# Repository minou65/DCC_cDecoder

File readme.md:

# cDecoder
## Inhalt
- [cDecoder](#cdecoder)
  - [Inhalt](#inhalt)
  - [Funktionen](#funktionen)
  - [Programmierung](#programmierung)
  - [Analog Betrieb](#analog-betrieb)
  - [Immer ein](#immer-ein)
  - [Powerpack](#powerpack)
  - [Dimmen der Ausgänge](#dimmen-der-ausgänge)
  - [Anschlüsse](#anschlüsse)
    - [fDecoder](#fdecoder)
    - [cDecoder](#cdecoder-1)
    - [PowerPack](#powerpack-1)
    - [Farben](#farben)
  - [Lange DCC Adresse](#lange-dcc-adresse)
  - [CV Tabelle](#cv-tabelle)
    - [Zuordnung Ausgänge zu Funktionstasten](#zuordnung-ausgänge-zu-funktionstasten)
    - [Funktion aktiv bei](#funktion-aktiv-bei)
    - [Modus der Ausgänge](#modus-der-ausgänge)
      - [Blinker On Time](#blinker-on-time)
      - [Blinker off Time](#blinker-off-time)
      - [Dimmen der Ausgänge](#dimmen-der-ausgänge-1)
      - [Automatisches abschalten](#automatisches-abschalten)
  - [Beispiele](#beispiele)
  - [Programmieren des prozessors](#programmieren-des-prozessors)

## Funktionen
- Ein/Aus
- Impuls
- Blinker

Der Attiny85 untersützt nur 5 Ausgänge. Die Funktionen sind auf die Ausgänge verteilt. Die Funktionen können über die CV's 66 - 70 eingestellt werden. 
Die Blinkerfunktion kann über die CV's 71 - 75 eingestellt werden. Die Zeit für das Blinken kann über die CV's 76 - 80 eingestellt werden. 
Die Zeit wird in 10ms Schritten angegeben. Die Helligkeit der Ausgänge kann über die CV's 81 und 82 eingestellt werden. 
Die Zeit für das automatische abschalten kann über die CV's 86 - 90 eingestellt werden. Die Zeit wird in 10ms Schritten angegeben.

## Programmierung
Um den Decoder auf dem Programmiergleis programmieren zu können muss eine Last an AUX 1 angeschlossen werden, die mindestens einen Strom von 60mA erzeugt.

## Analog Betrieb
Wird während 100ms kein DCC Signal erkannt, werden die Funktionen gemäss CV 13 aktiviert

## Immer ein
Ab Version 3 untersützt die Firmware CV 123, damit können Ausgänge definiert werden, welche beim anlagen einer Spannung sofort eingeschaltet werden.
Eingeführt für die Rheinbrücke beim Modell Eisenbahn Club Seebezirk (MECS), Fräschels (CH)

## Powerpack
Ein externes Powerpack kann an den Decoder angeschlossen werden. Dazu können die Pad's VCC und GND auf der Rückseite des Decoders verwendet werden.

## Dimmen der Ausgänge
Die Ausgänge AUX 1 und AUX 2 können gedimmt werden. Die Helligkeit kann über CV 81 und 82 eingestellt werden.

## Anschlüsse
### fDecoder
| oben | unten |
|---|---|
|  |  |
| __v2__ <br>  | |

### cDecoder
| oben | unten |
|---|---|
| ||

### PowerPack
| oben | unten |
|---|---|
|  ||

### Farben
| Draht | Verwendung |
|--------|--------------|
| Rot | Rail |
| Braun | Rail |
| Blau | Decoder + |
| Weiss | Aux 1 / Licht vorne |
| Gelb | Aux 2 / Licht hinten |
| Violett | Aux 3 |
| Grün | Aux 4 |
| Schwarz | GND |

## Lange DCC Adresse
Um die lange DCC-Adresse in die Register 17 und 18 umzurechnen, kann folgende Formel verwendet werden.<br><br>
CV 17 = Adresse / 256 (nur die Stellen vor dem Komma) + 192<br>
CV 18 = Adresse - ((CV 17 - 192) * 256)<br>

Die lange Adresse wird nur verwendet, wenn das Bit 5 in CV 29 gesetzt ist

Hier gibt es einen CV Rechner
https://www.opendcc.de/info/decoder/dcc_cv.html

## CV Tabelle
| Bezeichnung | CV | Wertbereich <br> (default) | Beschreibung |
|---|:--------:|---|---|
| Basisadresse | 1 | 1 - 255 (3) | Wertebereich im DCC-Format 1 - 127 |
| | 2 | 120 | |
| | 5 | 255 | |
| Version | 7 | | |
| Hersteller | 8 | | |
| Reset | 8 |  | Durch Eingeben eines Wertes 8, werden alle Einstellungen auf Default gesetzt |
| Im Analogbetrieb aktive Ausgänge | 13 | 0 - 255 (0) | AUX 1 ein = 1<br>AUX 2 ein = 2<br>AUX 3 ein = 4<br>AUX 4 ein = 8<br>AUX 5 ein = 16 |
| Decoderlock | 15 | 0 - 255 (0) | Decoder-Lock Funktion laut NMRA. <br>Details siehe http://www.nmra.org/standards/DCC/WGpublic/0305051/0305051.html |
| Decoderlock | 16 | 0 - 255 (0) | Decoder-Lock Funktion laut NMRA. <br>Details siehe http://www.nmra.org/standards/DCC/WGpublic/0305051/0305051.html |
| Erweiterte Adresse | 17 | 192 - 255 (0) | Nur für DCC-Format. Bei den meisten Zentralen ist es möglich, <br> erweiterte Adressendirekt einzugeben. Die CVs 17, 18 und 29 <br> werden von der Zentrale automatisch richtig eingestellt. |
| Erweiterte Adresse | 18 | 0 - 255 (3) |
| Konfigurationsdaten | 29 | 0 - 64 (2) | Fahrtrichtung Standard = 0 <br>Fahrtrichtung invertiert = 1 <br>14 Fahrstufen = 0 <br>28 oder 128 Fahrstufen 2 <br>Basisadressen = 0 <br>Erweiterte Adressen = 32 |
| Betriebszustand | 122 | 0/1 (0) | Den Betriebszustand der Ausgänge speichern. <br>0 = Aus <br>1 = Ein |
| Immer eingeschaltet<br>(ab Version 3) | 123 | 0 - 255 (0) | AUX 1 ein = 1<br>AUX 2 ein = 2<br>AUX 3 ein = 4<br>AUX 4 ein = 8<br>AUX 5 ein = 16 |

### Zuordnung Ausgänge zu Funktionstasten
| Bezeichnung | CV | Wertbereich <br> (default) | Beschreibung |
|---|:--------:|---|---|
| F0 | 30 | 0 - 31 (3) | AUX 1 = 1 <br> AUX 2 = 2 <br> AUX 3 = 4 <br> AUX 4 = 8 <br> AUX 5 = 16 |
| F1 | 31 | 0 - 31 (4) | |
| F2 | 32 | 0 - 31 (8) | |
| ... | ... | 0 - 31 (0) | |
| F28 | 58 | 0 - 31 (0) | |

### Funktion aktiv bei
| Bezeichnung | CV | Wertbereich <br> (default) | Beschreibung |
|---|:--------:|---|---|
| AUX 1 | 61 | 0 - 31 (1) | Vorwärts = 0 <br> Rückwärts = 1 <br> Beide = 3 <br> Default bei cDecoder ist 3 |
| AUX 2 | 62 | 0 - 31 (2) | Default bei cDecoder ist 3 |
| AUX 3 | 63 | 0 - 31 (3) | |
| AUX 4 | 64 | 0 - 31 (3) | |
| AUX 5 | 65 | 0 - 31 (3) | |

### Modus der Ausgänge
| Bezeichnung | CV | Wertbereich <br> (default) | Beschreibung |
|---|:--------:|---|---|
| AUX 1 | 66 | 0 - 31 (1) | Ein / Aus = 1 <br> Blinker = 2 <br> Impuls = 3 |
| AUX 2 | 67 | 0 - 31 (1) | |
| AUX 3 | 68 | 0 - 31 (1) | |
| AUX 4 | 69 | 0 - 31 (2) | |
| AUX 5 | 70 | 0 - 31 (2) | |

#### Blinker On Time
| Bezeichnung | CV | Wertbereich <br> (default) | Beschreibung |
|---|:--------:|---|---|
| AUX 1 | 71 | 0 - 255 (100) | Wert x 10 = Zeit in milli Sekunden |
| AUX 2 | 72 | 0 - 255 (100) | |
| AUX 3 | 73 | 0 - 255 (100) | |
| AUX 4 | 74 | 0 - 255 (100) | |
| AUX 5 | 75 | 0 - 255 (100) | |

#### Blinker off Time
| Bezeichnung | CV | Wertbereich <br> (default) | Beschreibung |
|---|:--------:|---|---|
| AUX 1 | 76 | 0 - 255 (100) | Wert x 10 = Zeit in milli Sekunden |
| AUX 2 | 77 | 0 - 255 (100) | |
| AUX 3 | 78 | 0 - 255 (100) | |
| AUX 4 | 79 | 0 - 255 (100) | |
| AUX 5 | 80 | 0 - 255 (100) | |

#### Dimmen der Ausgänge
| Bezeichnung | CV | Wertbereich <br> (default) | Beschreibung |
|---|:--------:|---|---|
| AUX 1 | 81 | 1 - 255 (255) | |
| AUX 2 | 82 | 1 - 255 (255) | |

#### Automatisches abschalten
| Bezeichnung | CV | Wertbereich <br> (default) | Beschreibung |
|---|:--------:|---|---|
| AUX 1 | 86 | 0 - 255 (0) | Wert x 10 = Zeit in milli Sekunden. Ist der <br> Wert grösser als 0 wird der Ausgang nach der <br> eingestellten Zeit wieder abgeschaltet. <br> Ist der Wert 0, dann bleibt der Ausgang eingeschaltet. |
| AUX 2 | 87 | 0 - 255 (0) | |
| AUX 3 | 88 | 0 - 255 (0) | |
| AUX 4 | 89 | 0 - 255 (0) | |
| AUX 5 | 90 | 0 - 255 (0) | |

## Beispiele
|Beispiel | Einstellungen |
|---|---|
| SBB Schlusslicht an AUX 4 <br><br><br><br> | CV64 = 36<br>CV69 = 27 <br>CV74 = 1 (On Time)<br>CV79 = 70 (Off Time) |
| Rheinbrücke MESC<br>Rote LED soll immer blinken<br><br><br> | CV123 = 1<br>CV66 = 2<br>CV71 = 80<br>76 = 20 |

## Programmieren des prozessors

Um den Prozessor zu programmieren wird ein ISP Programmer benötigt. Der Prozessor kann mit der Arduino IDE programmiert werden. Dazu muss der Prozessor als Board hinzugefügt werden.
- Dazu unter Datei -> Voreinstellungen -> Zusätzliche Boardverwalter-URLs: https://raw.githubusercontent.com/damellis/attiny/ide-1.6.x-boards-manager/package_damellis_attiny_index.json einfügen.
- Arduino AVR Boards installieren unter Werkzeuge -> Board -> Boardverwalter... -> Arduino AVR Boards installieren.
- In der Arduino IDE unter Werkzeuge -> Board -> Boardverwalter... -> attiny auswählen und installieren. 

Danach das Board wie folgt konfigurieren
    Board    : Attiny25/45/85
    Prozessor: Attiny85
    Clock    : Internal 16Mhz
    Programmer: Diamex USB ISP oder ATMEL STK500 (Für Windows 10 ist kein Treiber erforderlich)

Nun kann zuerst der Bootloader und danach die Firmware auf den Prozessor geschrieben werden. Unter visual Micro kommt folgende Fehlermeldung beim schreiben des Bootloaders

```
Error while burning bootloader.
Burn failed
avrdude: can't open input file aders/{bootloader.file}: No such file or directory
avrdude: read from file oaders/{bootloader.file}' failed
```

Dies ist normal, der Attiny hat keine Bootloader visual Micro sucht diesen aber und findet ihn nicht. Die Fuse und Clock settings werden aber geschrieben bevor der Bootloader geschrieben wird.
https://www.visualmicro.com/forums/YaBB.pl?num=1607630288

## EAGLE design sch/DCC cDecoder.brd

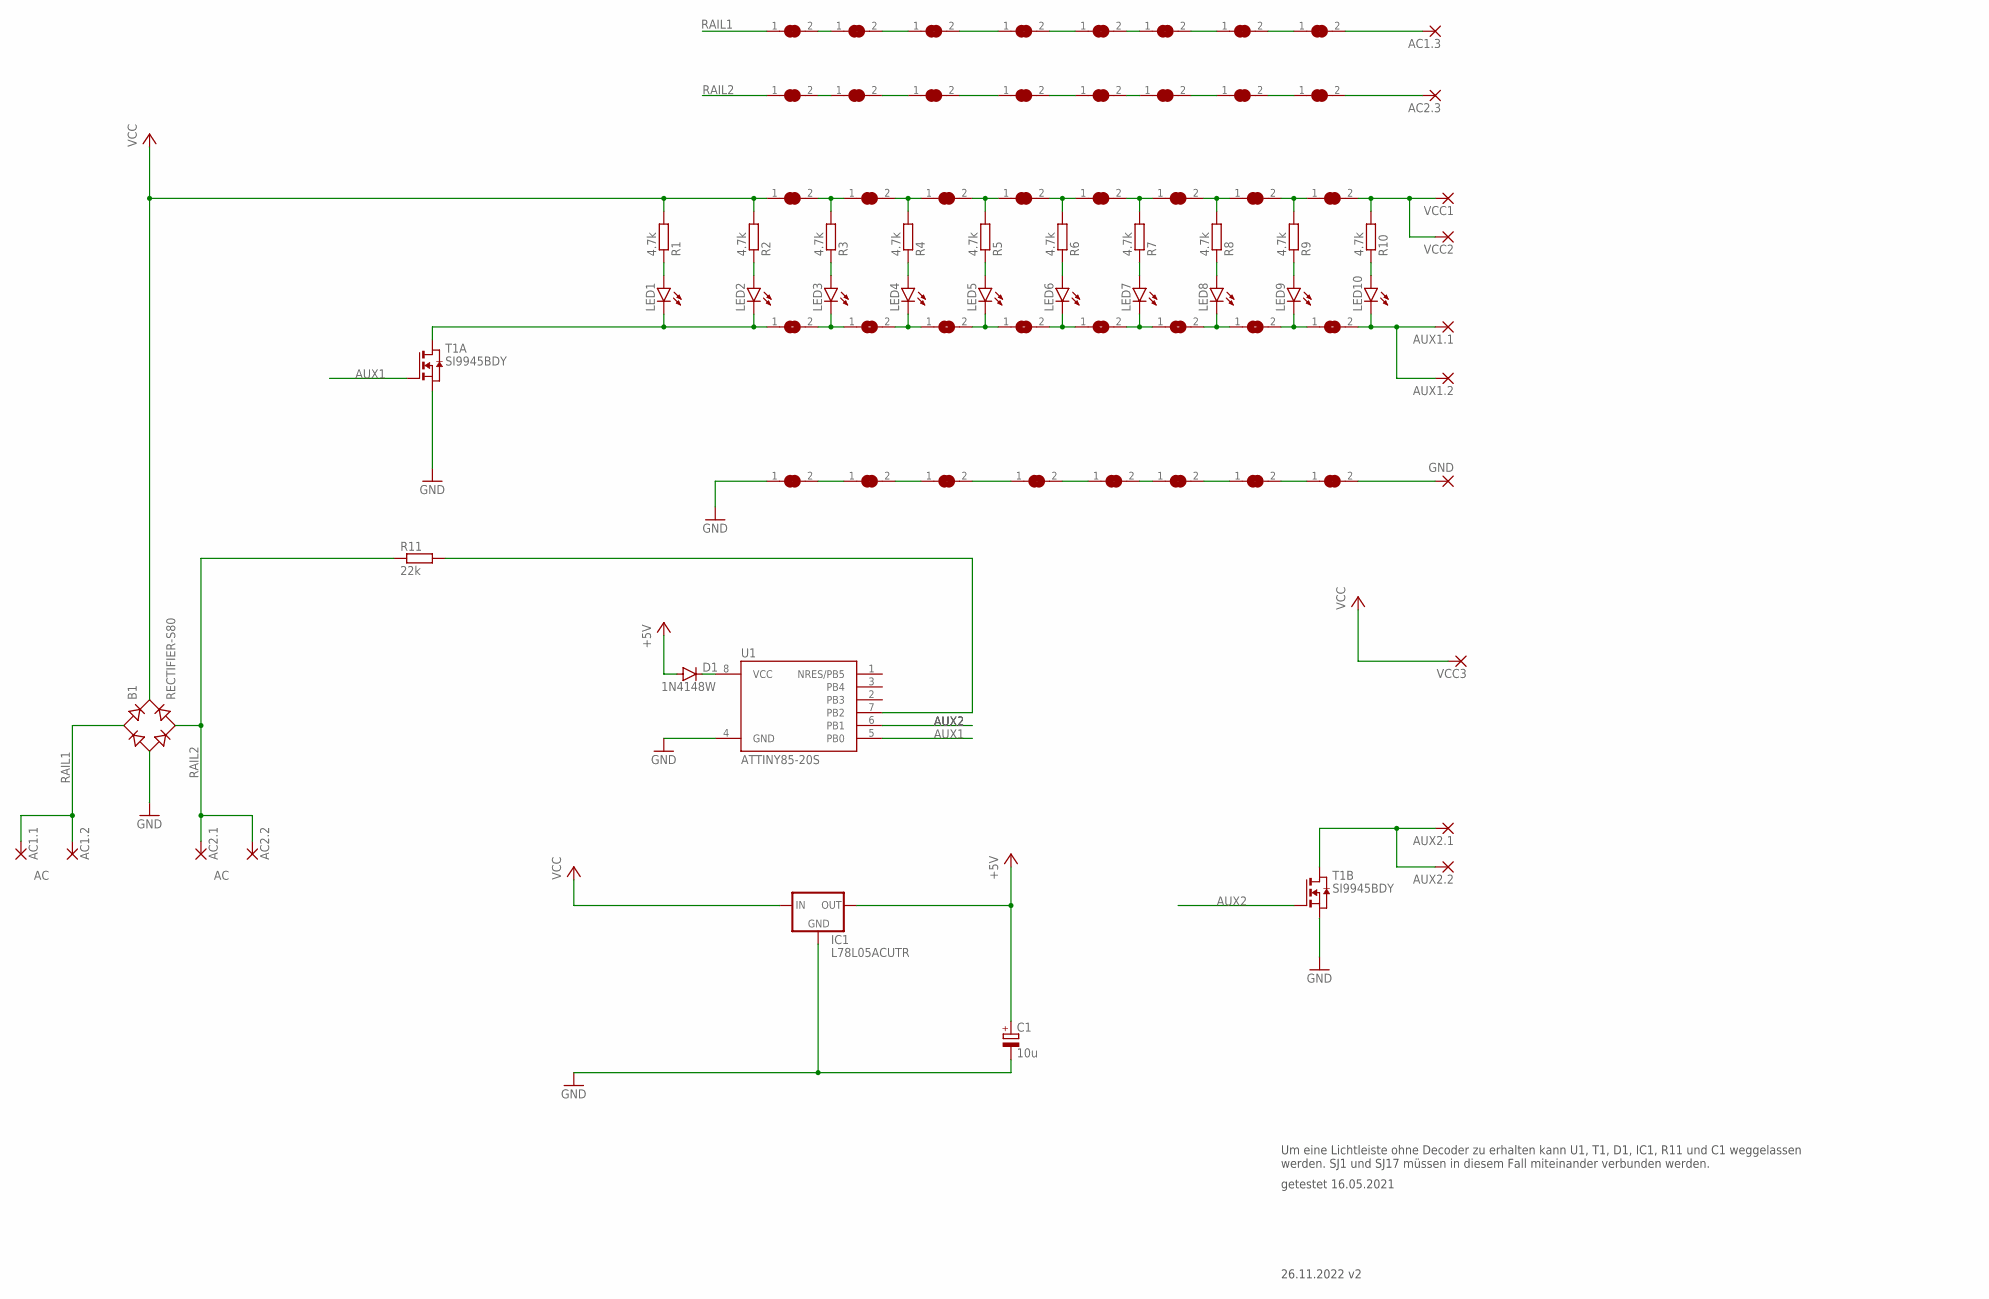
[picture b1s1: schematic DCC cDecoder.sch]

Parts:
AC1.1: AC1.1; SMD1,27-2,54
AC1.2: AC1.2; SMD1,27-2,54
AC1.3: AC1.3; SMD1,27-2,54
AC2.1: AC2.1; SMD1,27-2,54
AC2.2: AC2.2; SMD1,27-2,54
AC2.3: AC2.3; SMD1,27-2,54
AUX1.1: AUX1.1; SMD1,27-2,54
AUX1.2: AUX1.2; SMD1,27-2,54
AUX2.1: AUX2.1; SMD1,27-2,54
AUX2.2: AUX2.2; SMD1,27-2,54
B1: RECTIFIER-S80; TO-269AA
C1: 10u; A/3216-18W
D1: 1N4148W; SOD-123_MINI-SMA
GND: SMD2; SMD1,27-2,54
IC1: L78L05ACUTR; SOT89R
LED1, LED2, LED3, LED4, LED5, LED6, LED7, LED8, LED9, LED10: LEDCHIPLED_0805; CHIPLED_0805
R1, R2, R3, R4, R5, R6, R7, R8, R9, R10: 4.7k; R0805
R11: 22k; R0805
SJ1, SJ2, SJ3, SJ4, SJ5, SJ6, SJ7, SJ8, SJ9, SJ10, SJ11, SJ12, SJ13, SJ14, SJ15, SJ16, SJ25, SJ26, SJ27, SJ28, SJ29, SJ30, SJ31, SJ32, SJ33, SJ34, SJ35, SJ36, SJ37, SJ38, SJ39, SJ40: SJC
SJ17, SJ18, SJ19, SJ20, SJ21, SJ22, SJ23, SJ24: SJ
T1: SI9945BDY; SO8
U1: ATTINY85-20S; SOIC8_EIAJ_208MIL
VCC1: VCC1; SMD1,27-2,54
VCC2: VCC2; SMD1,27-2,54
VCC3: VCC3; SMD1,27-2,54

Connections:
+5V: C1.+, D1.A, IC1.2 (OUT)
AUX1: T1.2 (G), U1.5 (PB0)
AUX2: T1.4 (G), U1.6 (PB1)
GND: B1.-, C1.-, IC1.3 (GND), IC1.4 (GND), SJ1.1, T1.1 (S), T1.3 (S), U1.4 (GND)
unnamed: LED2.A, R2.1
unnamed: LED1.A, R1.1
unnamed: R3.2, SJ2.2, SJ4.1
unnamed: LED4.A, R4.1
unnamed: LED3.A, R3.1
unnamed: R6.2, SJ8.2, SJ10.1
unnamed: R7.2, SJ10.2, SJ12.1
unnamed: R8.2, SJ12.2, SJ14.1
unnamed: R9.2, SJ14.2, SJ16.1
unnamed: LED6.A, R6.1
unnamed: SJ1.2, SJ3.1
unnamed: R4.2, SJ4.2, SJ6.1
unnamed: LED7.A, R7.1
unnamed: LED8.A, R8.1
unnamed: AUX2.1.1, AUX2.2.1, T1.5 (D), T1.6 (D)
unnamed: SJ3.2, SJ5.1
unnamed: R5.2, SJ6.2, SJ8.1
unnamed: SJ5.2, SJ7.1
unnamed: LED3.C, SJ17.2, SJ18.1
unnamed: SJ7.2, SJ9.1
unnamed: LED5.A, R5.1
unnamed: SJ9.2, SJ11.1
unnamed: LED4.C, SJ18.2, SJ19.1
unnamed: SJ11.2, SJ13.1
unnamed: LED9.A, R9.1
unnamed: SJ13.2, SJ15.1
unnamed: LED10.A, R10.1
unnamed: GND.1, SJ15.2
unnamed: LED6.C, SJ20.2, SJ21.1
unnamed: D1.C, U1.8 (VCC)
unnamed: R10.2, SJ16.2, VCC1.1, VCC2.1
unnamed: LED5.C, SJ19.2, SJ20.1
unnamed: R11.2, U1.7 (PB2)
unnamed: AUX1.1.1, AUX1.2.1, LED10.C, SJ24.2
unnamed: LED7.C, SJ21.2, SJ22.1
unnamed: LED8.C, SJ22.2, SJ23.1
unnamed: LED9.C, SJ23.2, SJ24.1
unnamed: LED1.C, LED2.C, SJ17.1, T1.7 (D), T1.8 (D)
unnamed: SJ25.2, SJ26.1
unnamed: SJ26.2, SJ27.1
unnamed: SJ27.2, SJ28.1
unnamed: SJ28.2, SJ29.1
unnamed: SJ29.2, SJ30.1
unnamed: SJ30.2, SJ31.1
unnamed: SJ31.2, SJ32.1
unnamed: AC1.3.1, SJ32.2
unnamed: SJ33.2, SJ34.1
unnamed: SJ34.2, SJ35.1
unnamed: SJ35.2, SJ36.1
unnamed: SJ36.2, SJ37.1
unnamed: SJ37.2, SJ38.1
unnamed: SJ38.2, SJ39.1
unnamed: SJ39.2, SJ40.1
unnamed: AC2.3.1, SJ40.2
RAIL1: AC1.1.1, AC1.2.1, B1.AC1, SJ25.1
RAIL2: AC2.1.1, AC2.2.1, B1.AC2, R11.1, SJ33.1
VCC: B1.+, IC1.1 (IN), R1.2, R2.2, SJ2.1, VCC3.1

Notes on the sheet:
getestet 16.05.2021
Um eine Lichtleiste ohne Decoder zu erhalten kann U1, T1, D1, IC1, R11 und C1 weggelassen werden. SJ1 und SJ17 müssen in diesem Fall miteinander verbunden werden.
26.11.2022 v2

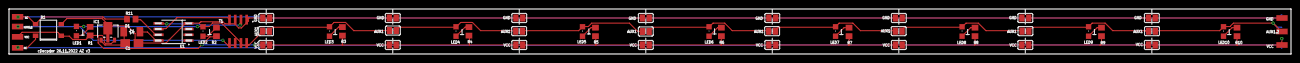
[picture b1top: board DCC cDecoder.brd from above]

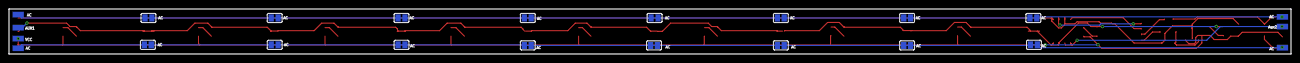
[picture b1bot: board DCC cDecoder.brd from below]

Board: 2 copper layers, 285.0 x 10.0 mm, 81 parts (23 on the bottom side), 61 nets.

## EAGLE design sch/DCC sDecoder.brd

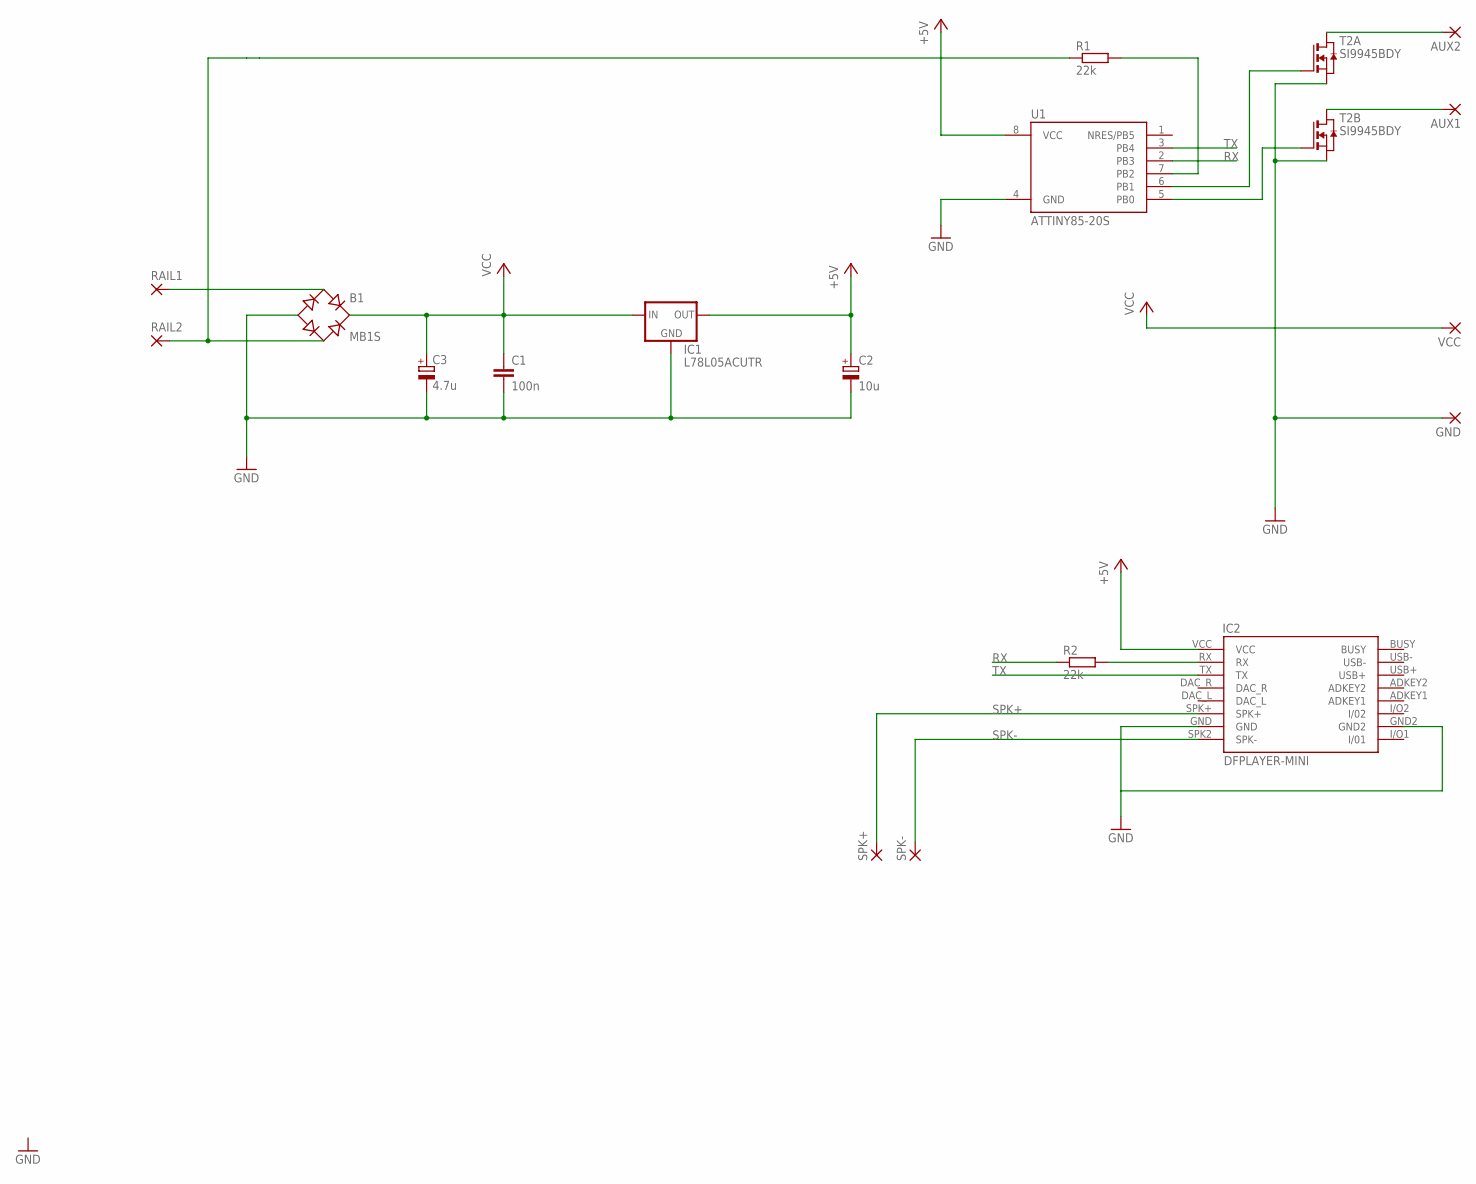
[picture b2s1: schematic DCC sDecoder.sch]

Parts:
AUX1, AUX2: SMD2; SMD1,27-2,54
B1: MB1S; SOIC-4
C1: 100n; C0805
C2: 10u; A/3216-18W
C3: 4.7u; A/3216-18W
GND: SMD2; SMD1,27-2,54
IC1: L78L05ACUTR; SOT89R
IC2: DFPLAYER-MINI
R1, R2: 22k; R0805
RAIL1, RAIL2: SMD2; SMD1,27-2,54
SPK+: SMD2; SMD1,27-2,54
SPK-: SMD2; SMD1,27-2,54
T2: SI9945BDY; SO8
U1: ATTINY85-20S; SOIC8_EIAJ_208MIL
VCC: SMD2; SMD1,27-2,54

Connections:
+5V: C2.+, IC1.2 (OUT), IC2.VCC, U1.8 (VCC)
GND: B1.-, C1.2, C2.-, C3.-, GND.1, IC1.3 (GND), IC1.4 (GND), IC2.GND, IC2.GND2, T2.1 (S), T2.3 (S), U1.4 (GND)
unnamed: IC2.RX, R2.2
unnamed: AUX2.1, T2.7 (D), T2.8 (D)
unnamed: AUX1.1, T2.5 (D), T2.6 (D)
unnamed: T2.4 (G), U1.5 (PB0)
unnamed: T2.2 (G), U1.6 (PB1)
unnamed: B1.~2 (AC2), R1.1, RAIL2.1
unnamed: R1.2, U1.7 (PB2)
unnamed: B1.~1 (AC1), RAIL1.1
RX: R2.1, U1.2 (PB3)
SPK+: IC2.SPK+, SPK+.1
SPK-: IC2.SPK2 (SPK-), SPK-.1
TX: IC2.TX, U1.3 (PB4)
VCC: B1.+, C1.1, C3.+, IC1.1 (IN), VCC.1

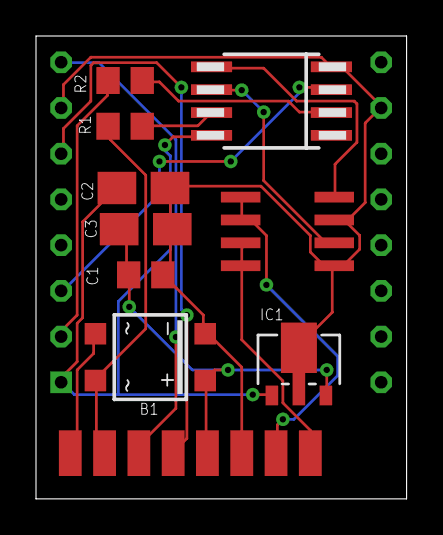
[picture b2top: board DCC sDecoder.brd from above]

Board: 2 copper layers, 20.6 x 25.7 mm, 18 parts (1 on the bottom side), 15 nets.

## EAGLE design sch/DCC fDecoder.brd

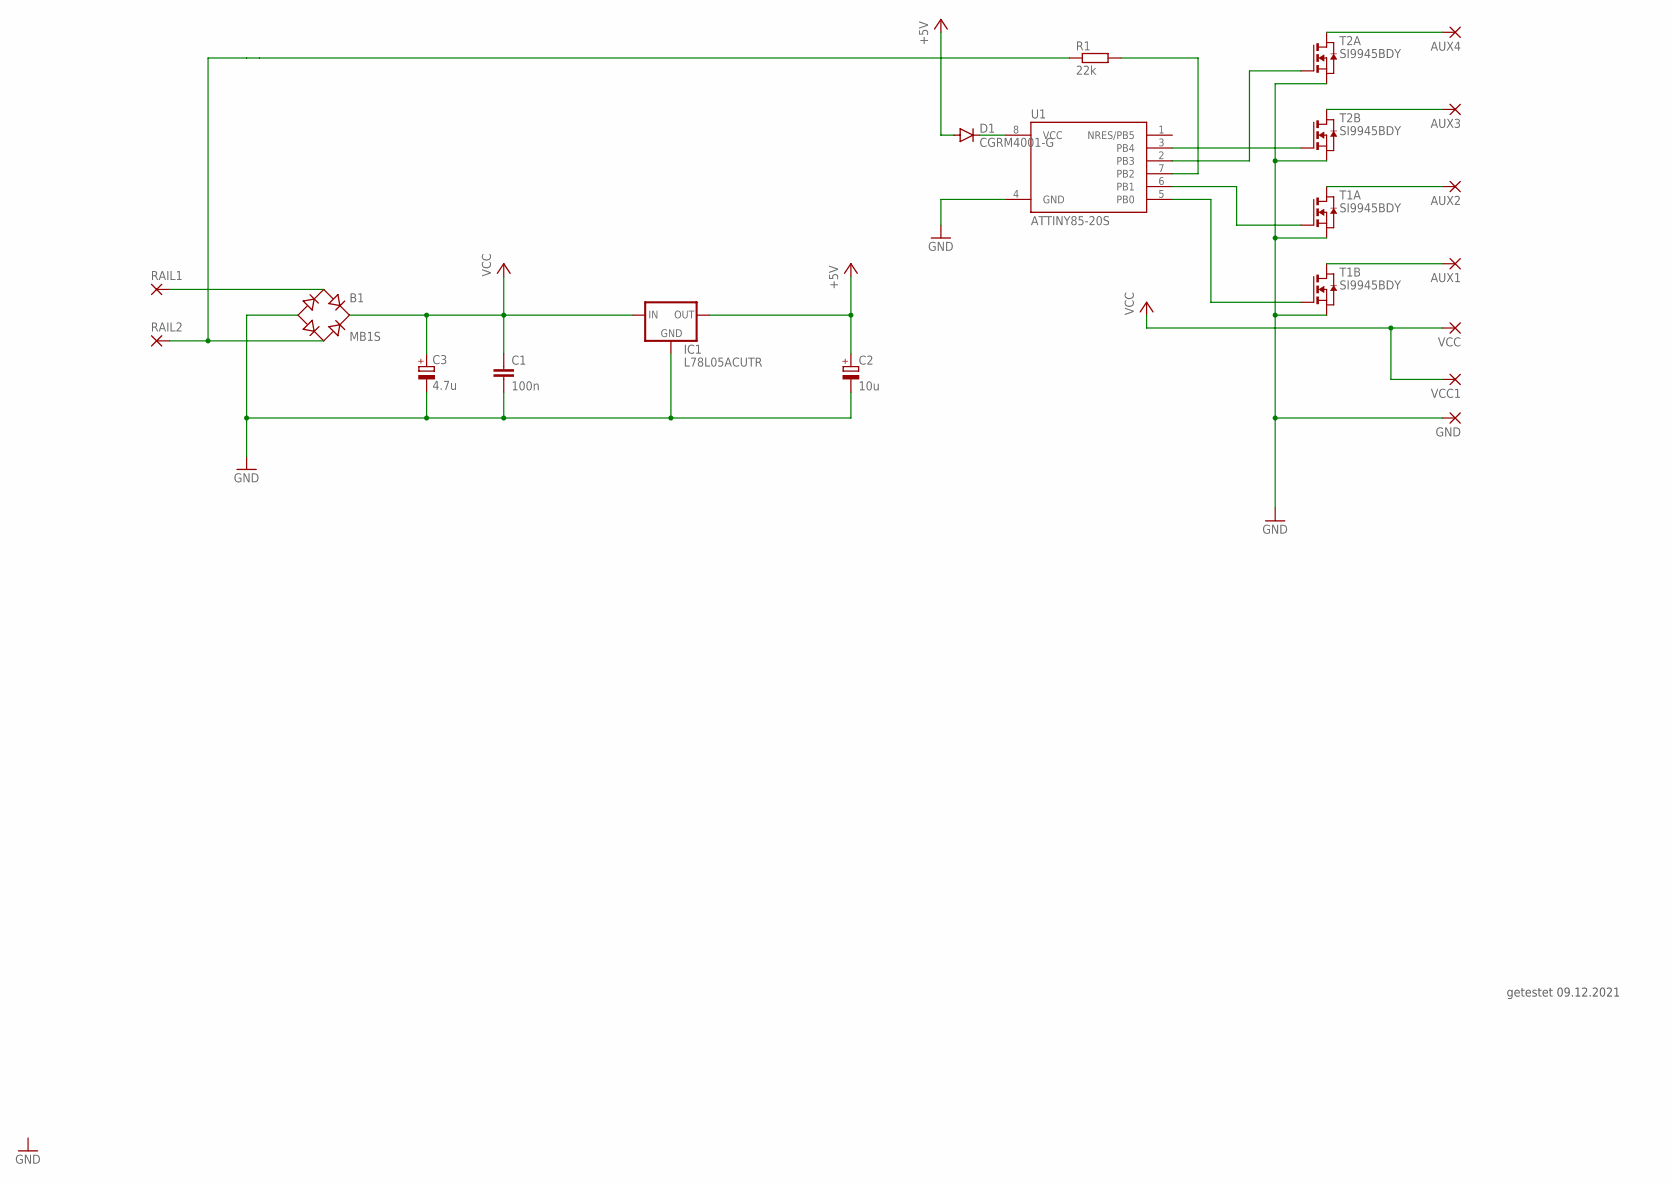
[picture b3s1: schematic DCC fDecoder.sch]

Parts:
AUX1, AUX2, AUX3, AUX4: SMD2; SMD1,27-2,54
B1: MB1S; SOIC-4
C1: 100n; C0805
C2: 10u; A/3216-18W
C3: 4.7u; A/3216-18W
D1: CGRM4001-G; SOD-123_MINI-SMA
GND: SMD2; SMD1,27-2,54
IC1: L78L05ACUTR; SOT89R
R1: 22k; R0805
RAIL1, RAIL2: SMD2; SMD1,27-2,54
T1, T2: SI9945BDY; SO8
U1: ATTINY85-20S; SOIC8_EIAJ_208MIL
VCC, VCC1: SMD2; SMD1,27-2,54

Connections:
+5V: C2.+, D1.A, IC1.2 (OUT)
GND: B1.-, C1.2, C2.-, C3.-, GND.1, IC1.3 (GND), IC1.4 (GND), T1.1 (S), T1.3 (S), T2.1 (S), T2.3 (S), U1.4 (GND)
unnamed: AUX1.1, T1.5 (D), T1.6 (D)
unnamed: AUX4.1, T2.7 (D), T2.8 (D)
unnamed: AUX3.1, T2.5 (D), T2.6 (D)
unnamed: AUX2.1, T1.7 (D), T1.8 (D)
unnamed: T1.4 (G), U1.5 (PB0)
unnamed: T1.2 (G), U1.6 (PB1)
unnamed: T2.2 (G), U1.2 (PB3)
unnamed: T2.4 (G), U1.3 (PB4)
unnamed: D1.C, U1.8 (VCC)
unnamed: B1.~2 (AC2), R1.1, RAIL2.1
unnamed: R1.2, U1.7 (PB2)
unnamed: B1.~1 (AC1), RAIL1.1
VCC: B1.+, C1.1, C3.+, IC1.1 (IN), VCC.1, VCC1.1

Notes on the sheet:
getestet 09.12.2021

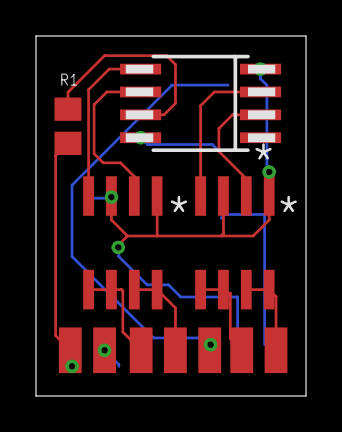
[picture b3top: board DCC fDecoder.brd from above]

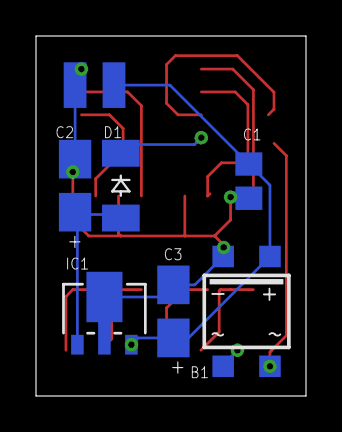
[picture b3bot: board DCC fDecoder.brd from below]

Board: 2 copper layers, 15.0 x 20.0 mm, 19 parts (8 on the bottom side), 15 nets.

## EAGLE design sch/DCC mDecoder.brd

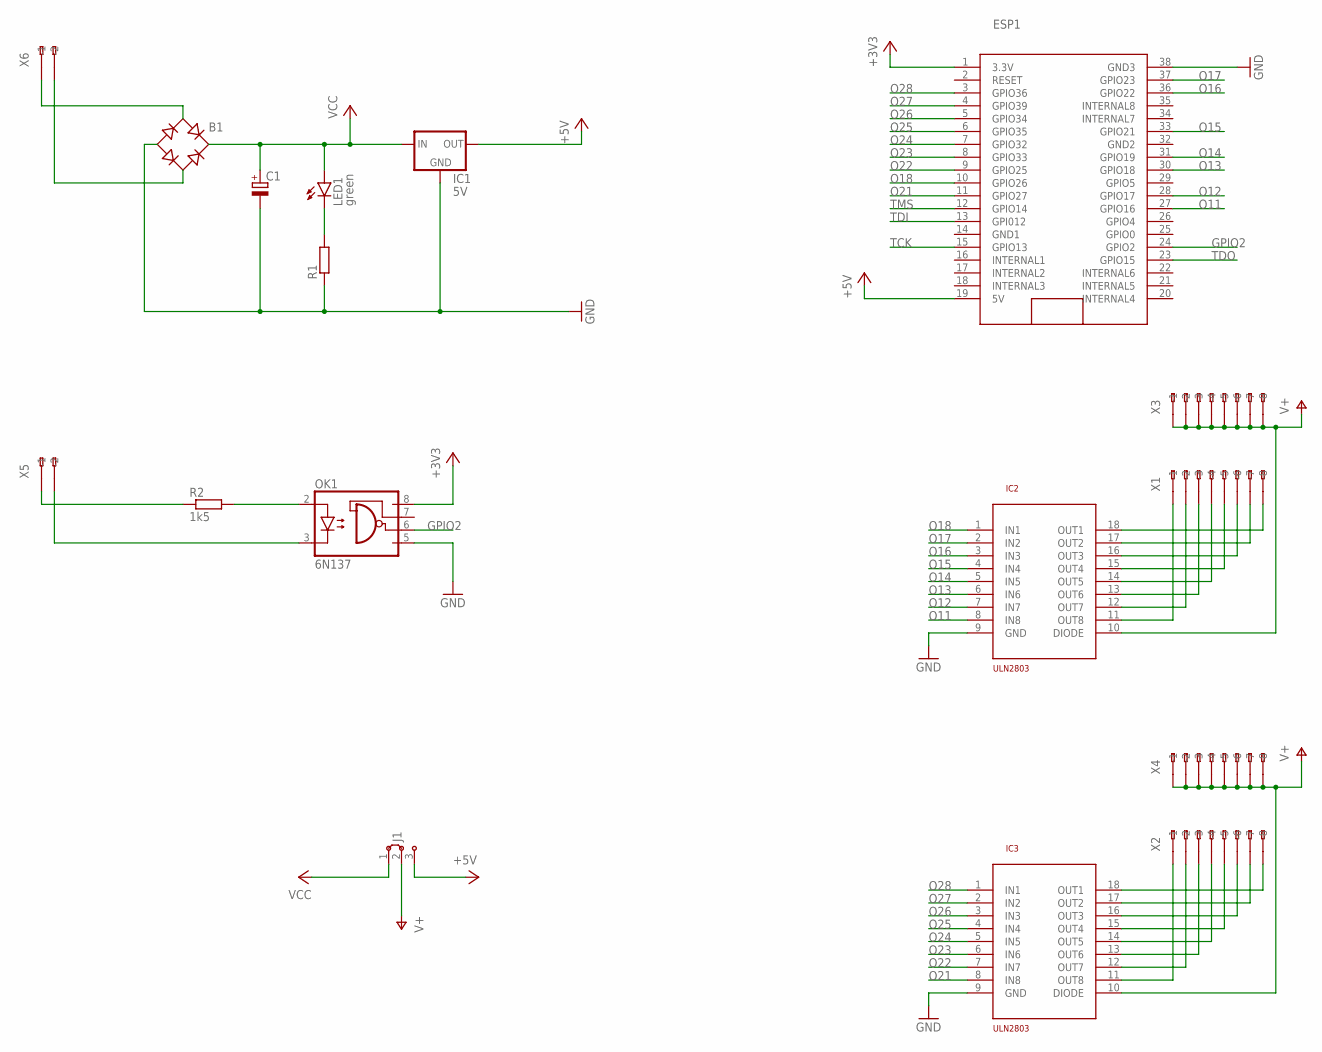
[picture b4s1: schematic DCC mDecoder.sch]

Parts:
B1: RB1A
C1: CPOL-EUE5-8.5; E5-8,5
ESP1: ESP32-NODEMCU; ESP32_NODEMCU
IC1: 5V; 78XXS
IC2, IC3: ULN2803; DIL18
J1: J2X2MM; 04C
LED1: green; LED3MM
OK1: 6N137; DIL08
R1: R-EU_0207/10; 0207/10
R2: 1k5; 0207/10
X1, X2, X3, X4: 233-508
X5, X6: 233-202

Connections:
+3V3: ESP1.1 (3.3V), OK1.8 (VCC)
+5V: ESP1.19 (5V), IC1.OUT, J1.3
GND: B1.-, C1.-, ESP1.38 (GND3), IC1.GND, IC2.9 (GND), IC3.9 (GND), OK1.5 (GND), R1.1
GND1: ESP1.14 (GND1)
GND2: ESP1.32 (GND2)
GPIO2: ESP1.24 (GPIO2), OK1.6 (VO)
unnamed: IC2.11 (OUT8), X1.A1 (-1)
unnamed: IC2.12 (OUT7), X1.A2 (-2)
unnamed: LED1.K (C), R1.2
unnamed: IC2.13 (OUT6), X1.A3 (-3)
unnamed: B1.AC1, X6.A1 (-1)
unnamed: B1.AC2, X6.A2 (-2)
unnamed: IC2.14 (OUT5), X1.A4 (-4)
unnamed: IC2.15 (OUT4), X1.A5 (-5)
unnamed: R2.1, X5.A1 (-1)
unnamed: OK1.2 (A), R2.2
unnamed: OK1.3 (C), X5.A2 (-2)
unnamed: IC2.16 (OUT3), X1.A6 (-6)
unnamed: IC2.17 (OUT2), X1.A7 (-7)
unnamed: IC2.18 (OUT1), X1.A8 (-8)
unnamed: IC3.18 (OUT1), X2.A8 (-8)
unnamed: IC3.17 (OUT2), X2.A7 (-7)
unnamed: IC3.16 (OUT3), X2.A6 (-6)
unnamed: IC3.15 (OUT4), X2.A5 (-5)
unnamed: IC3.14 (OUT5), X2.A4 (-4)
unnamed: IC3.13 (OUT6), X2.A3 (-3)
unnamed: IC3.12 (OUT7), X2.A2 (-2)
unnamed: IC3.11 (OUT8), X2.A1 (-1)
O11: ESP1.27 (GPIO16), IC2.8 (IN8)
O12: ESP1.28 (GPIO17), IC2.7 (IN7)
O13: ESP1.30 (GPIO18), IC2.6 (IN6)
O14: ESP1.31 (GPIO19), IC2.5 (IN5)
O15: ESP1.33 (GPIO21), IC2.4 (IN4)
O16: ESP1.36 (GPIO22), IC2.3 (IN3)
O17: ESP1.37 (GPIO23), IC2.2 (IN2)
O18: ESP1.10 (GPIO26), IC2.1 (IN1)
O21: ESP1.11 (GPIO27), IC3.8 (IN8)
O22: ESP1.9 (GPIO25), IC3.7 (IN7)
O23: ESP1.8 (GPIO33), IC3.6 (IN6)
O24: ESP1.7 (GPIO32), IC3.5 (IN5)
O25: ESP1.6 (GPIO35), IC3.4 (IN4)
O26: ESP1.5 (GPIO34), IC3.3 (IN3)
O27: ESP1.4 (GPIO39), IC3.2 (IN2)
O28: ESP1.3 (GPIO36), IC3.1 (IN1)
TCK: ESP1.15 (GPIO13)
TDI: ESP1.13 (GPI012)
TDO: ESP1.23 (GPIO15)
TMS: ESP1.12 (GPIO14)
V+: IC2.10 (DIODE), IC3.10 (DIODE), J1.2, X3.A1 (-1), X3.A2 (-2), X3.A3 (-3), X3.A4 (-4), X3.A5 (-5), X3.A6 (-6), X3.A7 (-7), X3.A8 (-8), X4.A1 (-1), X4.A2 (-2), X4.A3 (-3), X4.A4 (-4), X4.A5 (-5), X4.A6 (-6), X4.A7 (-7), X4.A8 (-8)
VCC: B1.+, C1.+, IC1.IN, J1.1, LED1.A

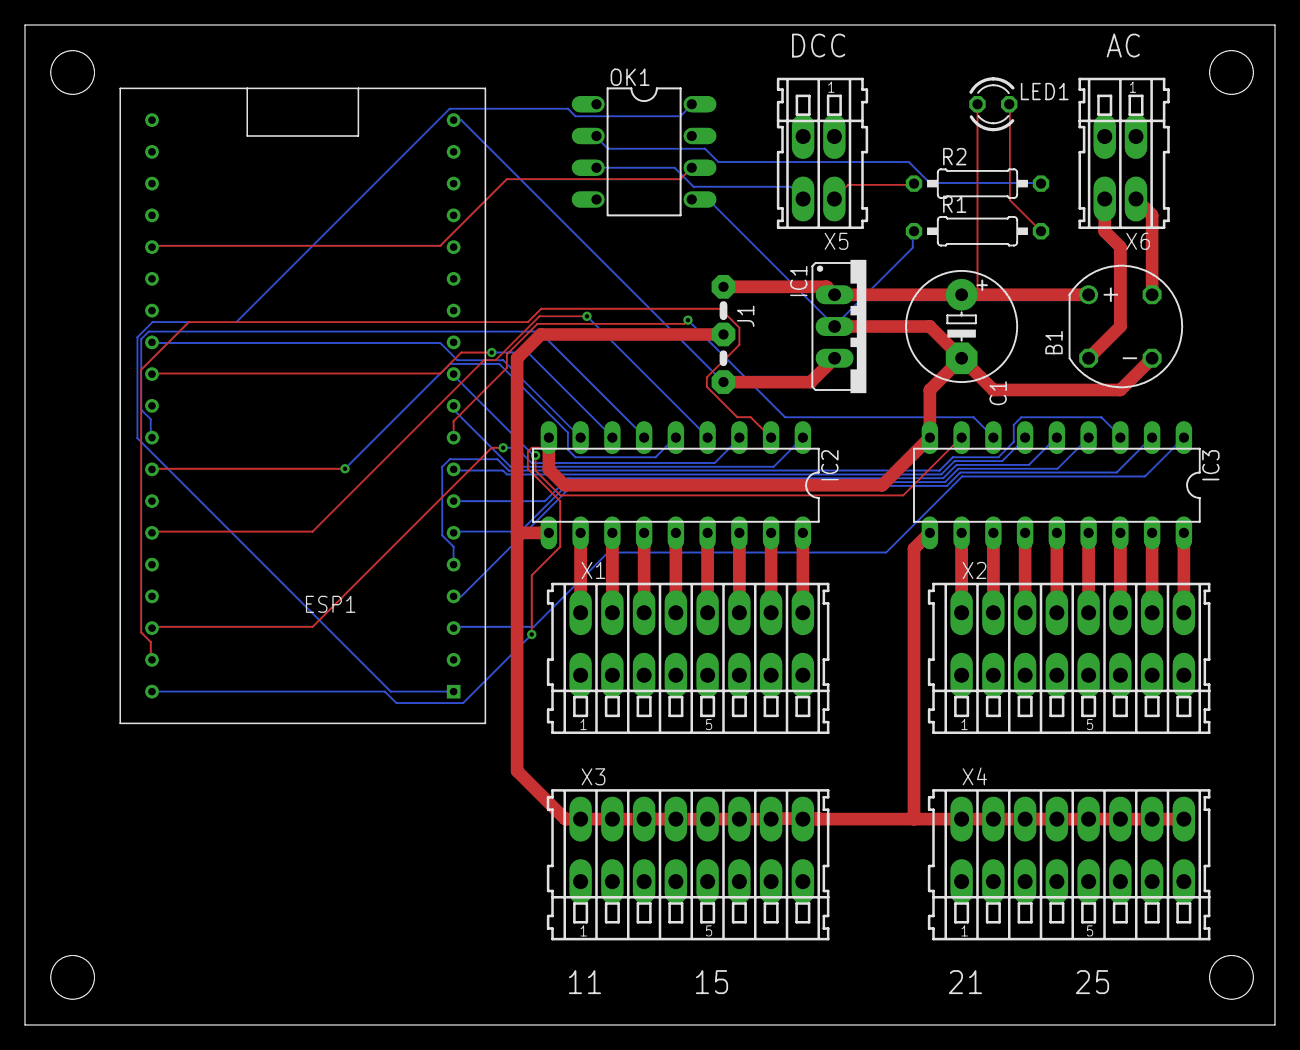
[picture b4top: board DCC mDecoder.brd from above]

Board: 2 copper layers, 100.0 x 80.0 mm, 17 parts (0 on the bottom side), 44 nets.

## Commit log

2023-10-27 initial version
2023-11-10 set all ports to output an disable them
2023-11-11 fixed typo
2023-12-04 version 2
2023-12-04 ignore /sch/*.s#*
2023-12-24 remove sound part
2023-12-24 layout v2
2023-12-24 new file
2024-03-06 file added
2024-03-06 removed cv's from main
2024-03-24 removed some help and moved to readme
2024-03-24 readme updated
2024-03-24 initial upload
2024-03-28 footprint mosfet changed (v3)
2024-03-28 allways on. Added for Modell Eisenbahn Club Seebezirk (MECS)
2024-03-28 Version 3
2024-03-29 reverted changes
2024-03-29 allways on added for Modell Eisenbahn Club Seebezirk (MECS)
2024-03-29 fixed bug for analog mode
2024-03-29 redme updated
2024-03-29 license added
2024-03-30 fixed wrong function key bitmap for F5 - F9
2024-03-31 Attiny85 suports only 4 outputs
2024-09-29 file updated
2024-10-01 migratet to new version ESPAsyncWebServer. Added some error handling for more stability
2026-01-23 Refactoring: Separate decoder core library from decoder logic
    Split code into reusable core library (ATtiny_DecoderCore.h)
    and decoder-specific implementation.
2026-01-23 Fix: Correct macro name from SOUND_DECODER to SOUND_FEATURE in DecoderCoreConfig.h
2026-01-25 removed file
2026-01-25 Add: Create PinConfig.h for pin configuration definitions
2026-01-25 Add: Create board.txt for attiny85 build extra flags
2026-01-25 Add: Include PinConfig.h for pin configuration definitions
2026-01-25 Remove unused Arduino includes and debug message definitions from DecoderCoreConfig.h
